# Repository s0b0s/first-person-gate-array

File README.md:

# First-Person Gate Array

A first-person shooter game built entirely from digital logic on a small FPGA board, with no
processor anywhere (no soft CPU, no microcontroller). The 3D renderer, monsters, game rules,
keyboard and mouse interface and sound are all state machines and memories written in VHDL.

## What the game is

Walk through a textured 3D maze, open doors, collect keys, health, ammo and weapons, and fight
monsters that see you, chase you and shoot back. Three levels, the last ending with a boss.
Each level has floor and ceiling heights, steps, ramps and pits, flickering and glowing
lights, outdoor areas with a sky, and animated slime walls. Gunfire wakes monsters in nearby
rooms, except those lying in ambush.

There is a status bar, a minimap, a full-screen automap, title, briefing and score screens,
and stereo sound effects and music.

## How it runs

- **Board:** Digilent Cmod A7-35T (a Xilinx Artix-7 FPGA with 512 KB of external SRAM and 4 MB
  of flash).
- **Video:** 320x240 pixels, each drawn as a 2x2 block on a standard 640x480, 60 Hz VGA monitor
  through a Digilent Pmod VGA. Colors come from a 256-entry palette.
- **Input:** a PS/2 keyboard and a PS/2 mouse through two Digilent Pmod PS2 boards.
- **Sound:** stereo through a Digilent Pmod I2S2 to headphones.
- **Boot:** the design and all game data load from the board's flash at power-up, so no PC is
  needed.

The modules plug into a small custom carrier PCB. Inside the FPGA, the main blocks are:

| Block | What it does |
| --- | --- |
| Ray engine | Casts one ray per screen column through the tile map to find the walls |
| Column rasterizer | Draws each column: walls, floors, ceilings, sky, lighting |
| Sprite engine | Draws monsters, items and projectiles, hidden correctly behind walls |
| Overlay | Status bar, minimap, automap and text screens |
| Game core | Player movement, collision, doors, monsters, weapons, pickups, levels |
| Display controller | Reads the finished frame from SRAM and sends it to the monitor |
| PS/2 host | Talks to the keyboard and mouse |
| Audio mixer | Mixes 8 sound effect voices and a music track |
| SRAM and flash controllers | Shared memory access and loading game data at boot |

Two frames live in SRAM: the game draws one while the monitor shows the other. Drawing takes
about 3 to 6 ms of the 16.8 ms frame (the 25 MHz pixel clock gives 59.5 Hz).

## Controls

| Action | Keys |
| --- | --- |
| Move forward / back | W / S, or the up / down arrows |
| Strafe | A / D |
| Turn | Mouse, or the left / right arrows |
| Fire | Left click, or Ctrl |
| Use (doors, switches) | Space |
| Run | Shift |
| Duck | Hold C |
| Peek left / right | Hold Q / E |
| Weapons | 1, 2, or right click to cycle |
| Automap | Tab |
| Pause | Esc |

## How it was built

The design grew in steps, each ending in a bitstream that builds and meets timing:

| In order | What it added | Top level |
| --- | --- | --- |
| Bring-up | Test patterns, SRAM and flash tests, raw keyboard and mouse codes, test tone, UART | `bringup_top` |
| First maze | A textured maze to walk through, with doors and collision | `game_top` |
| Full game | Monsters, weapons, items, keys, HUD, maps, sound, three levels | `shooter_top` |
| Heights | Floor and ceiling heights, steps, ramps, light effects, sky, animated walls | `shooter_top` |
| Alerts | Monsters woken by gunfire, and ambushing monsters | `shooter_top` |

## How it was checked

A Python model of the whole game (`tools/model/`) is the reference. It generates the
textures, levels and sounds and the "golden" frames, game states and audio samples. Every
hardware block has a self-checking testbench that matches the model bit for bit. The largest
test boots the complete design from a simulated flash chip and plays a scripted session.

## Repository layout

| Folder | Contents |
| --- | --- |
| `rtl/` | The hardware design (VHDL), one block per file |
| `sim/` | Simulation testbenches and models of the SRAM, flash, keyboard, mouse and monitor |
| `constraints/` | Pin assignments and timing constraints for the board |
| `scripts/` | Build the bitstream and run the simulations |
| `tools/` | Python: the game model, asset generators, flash image builder, style checkers, PC debug tools |
| `assets/levels/` | Text pictures of the three level maps, written by the model, so a person can read the levels |
| `build/` | Everything generated (not kept in git) |

## Building

You need Vivado 2025.1 (xsim runs the testbenches) and Python 3.9 or newer. The Python tools
use only the standard library, except the UART tools in `tools/uart/`: the debug tool needs
`pyserial` (`pip install -r requirements.txt`) and the live viewer also `pygame-ce`. With
[uv](https://docs.astral.sh/uv/), `uv run tools/uart/debug_uart.py ...` installs what each needs.
Run everything from the repository root.

On a fresh clone, run the first two steps first: they write the art, level and game-data
files into `build/` that the testbenches and the flash image read.

| Step | Command |
| --- | --- |
| Generate the assets, ROM contents and test data | `python tools/model/build_assets.py` |
| Build the flash game-data image | `python tools/flash_image/make_gamedata.py` |
| Run every testbench (the full-system test sets the pace) | `python scripts/run_sim.py` |
| Run only the testbenches whose inputs changed since they last passed | `python scripts/run_sim.py --changed` |
| Run some testbenches | `python scripts/run_sim.py tb_sram tb_ray_engine` |
| Check the code style | `python tools/style/check_vhdl_style.py` and `python tools/style/check_vhdl_structure.py` |
| Build the bitstream and flash image | `vivado -mode batch -source scripts/build.tcl -tclargs shooter_top` |

The build writes `build/shooter_top/shooter_top.bit` (load straight into the FPGA) and
`shooter_top.mcs` (program into flash so the game boots on its own). `bringup_top` (board and
wiring test pages) and `game_top` (the first playable maze) build the same way.

## Watching the game without a monitor

`tools/uart/live_view.py` (or double-click `tools/uart/live_view.bat`) shows the game in a
window over the board's USB cable, like a second monitor. It finds the board and the link rate
by itself and reconnects when the board is reset, reprogrammed or unplugged; close the window
to stop it. The board streams each new frame at 12 Mbaud, sending only the pixels that changed
since the frame before, run-length encoded, so the window keeps up with the game's 60 frames a
second; a whole new view while turning fast takes longer. Older bitstreams without the stream
command are read frame by frame instead. The keyboard and mouse stay on the board.
`tools/uart/debug_uart.py` reads and writes registers and memory, and its `capture` command
freezes the game for an exact frame dump.

## Art and sound

All textures, sprites, sounds and music are original, generated by `tools/model/`. No assets
from other games are used.

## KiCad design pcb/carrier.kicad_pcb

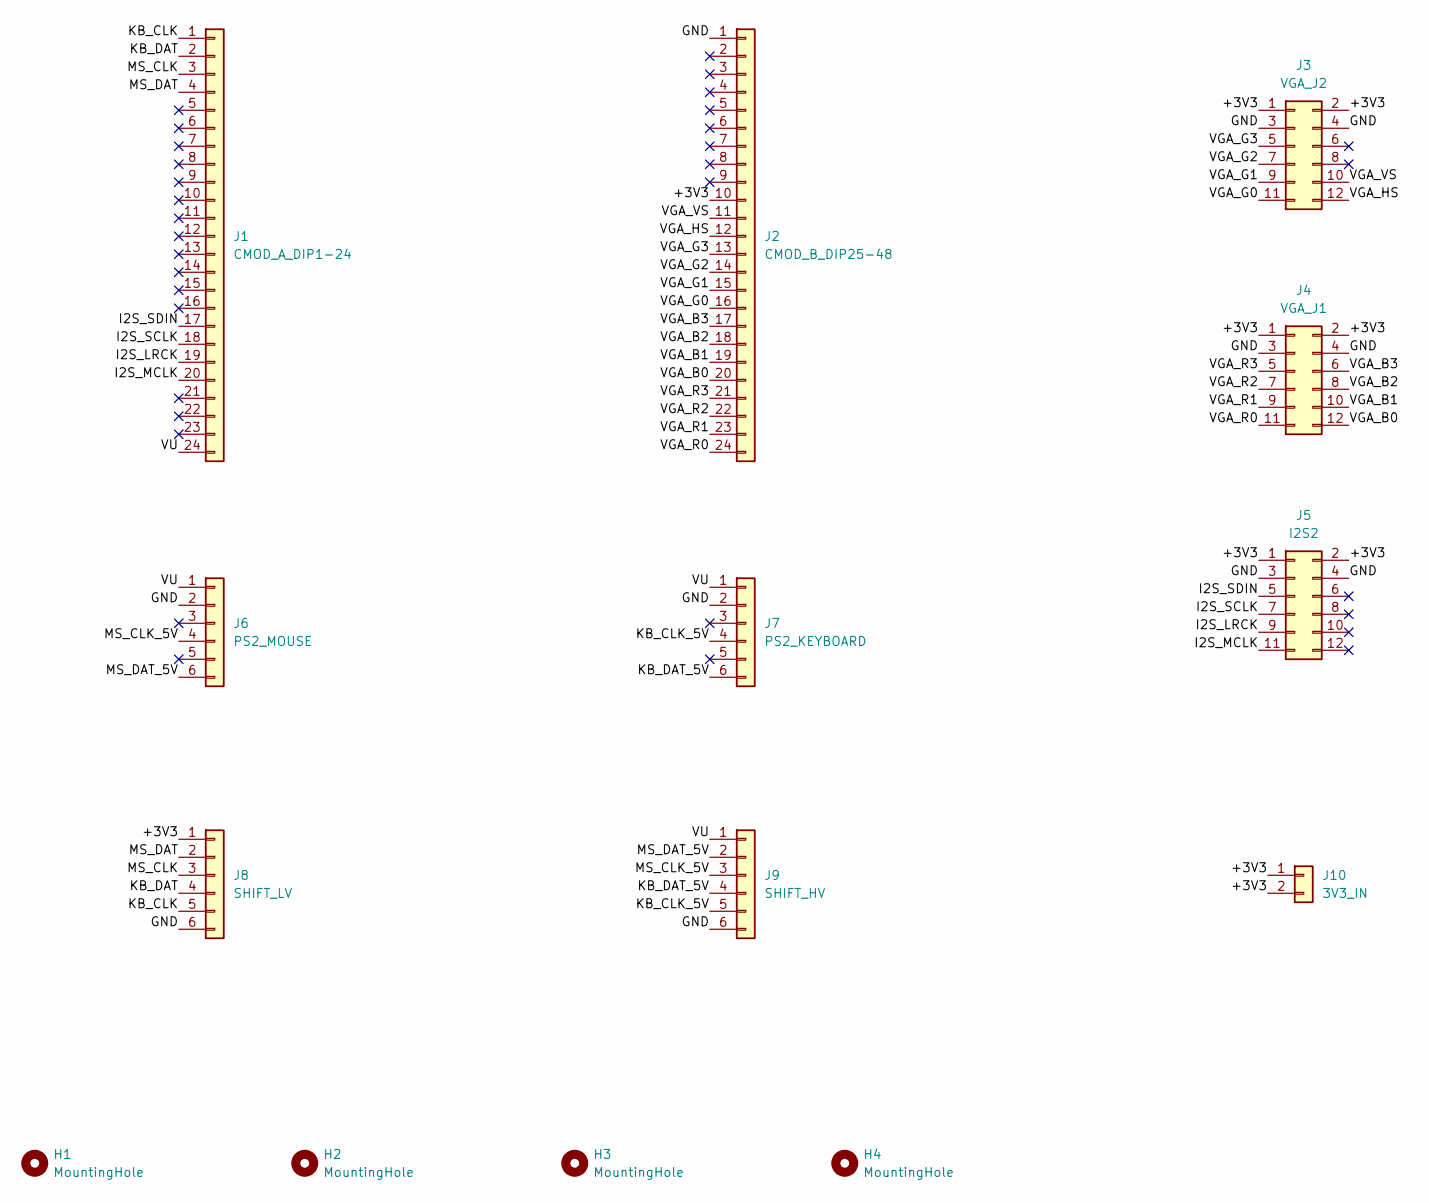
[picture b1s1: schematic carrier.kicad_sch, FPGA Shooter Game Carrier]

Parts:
H1, H2, H3, H4: MountingHole; MountingHole_3.2mm_M3
J1: CMOD_A_DIP1-24; PinSocket_1x24_P2.54mm_Vertical
J2: CMOD_B_DIP25-48; PinSocket_1x24_P2.54mm_Vertical
J3: VGA_J2; PinSocket_2x06_P2.54mm_Horizontal_Edge2mm
J4: VGA_J1; PinSocket_2x06_P2.54mm_Horizontal_Edge2mm
J5: I2S2; PinSocket_2x06_P2.54mm_Horizontal_Edge2mm
J6: PS2_MOUSE; PinSocket_1x06_P2.54mm_Horizontal_Edge2mm
J7: PS2_KEYBOARD; PinSocket_1x06_P2.54mm_Horizontal_Edge2mm
J8: SHIFT_LV; PinSocket_1x06_P2.54mm_Vertical
J9: SHIFT_HV; PinSocket_1x06_P2.54mm_Vertical
J10: 3V3_IN; PinSocket_1x02_P2.54mm_Vertical

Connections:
/+3V3: J2.10, J3.1, J3.2, J4.1, J4.2, J5.1, J5.2, J8.1, J10.1, J10.2
/GND: J2.1, J3.3, J3.4, J4.3, J4.4, J5.3, J5.4, J6.2, J7.2, J8.6, J9.6
/I2S_LRCK: J1.19, J5.9
/I2S_MCLK: J1.20, J5.11
/I2S_SCLK: J1.18, J5.7
/I2S_SDIN: J1.17, J5.5
/KB_CLK: J1.1, J8.5
/KB_CLK_5V: J7.4, J9.5
/KB_DAT: J1.2, J8.4
/KB_DAT_5V: J7.6, J9.4
/MS_CLK: J1.3, J8.3
/MS_CLK_5V: J6.4, J9.3
/MS_DAT: J1.4, J8.2
/MS_DAT_5V: J6.6, J9.2
/VGA_B0: J2.20, J4.12
/VGA_B1: J2.19, J4.10
/VGA_B2: J2.18, J4.8
/VGA_B3: J2.17, J4.6
/VGA_G0: J2.16, J3.11
/VGA_G1: J2.15, J3.9
/VGA_G2: J2.14, J3.7
/VGA_G3: J2.13, J3.5
/VGA_HS: J2.12, J3.12
/VGA_R0: J2.24, J4.11
/VGA_R1: J2.23, J4.9
/VGA_R2: J2.22, J4.7
/VGA_R3: J2.21, J4.5
/VGA_VS: J2.11, J3.10
/VU: J1.24, J6.1, J7.1, J9.1

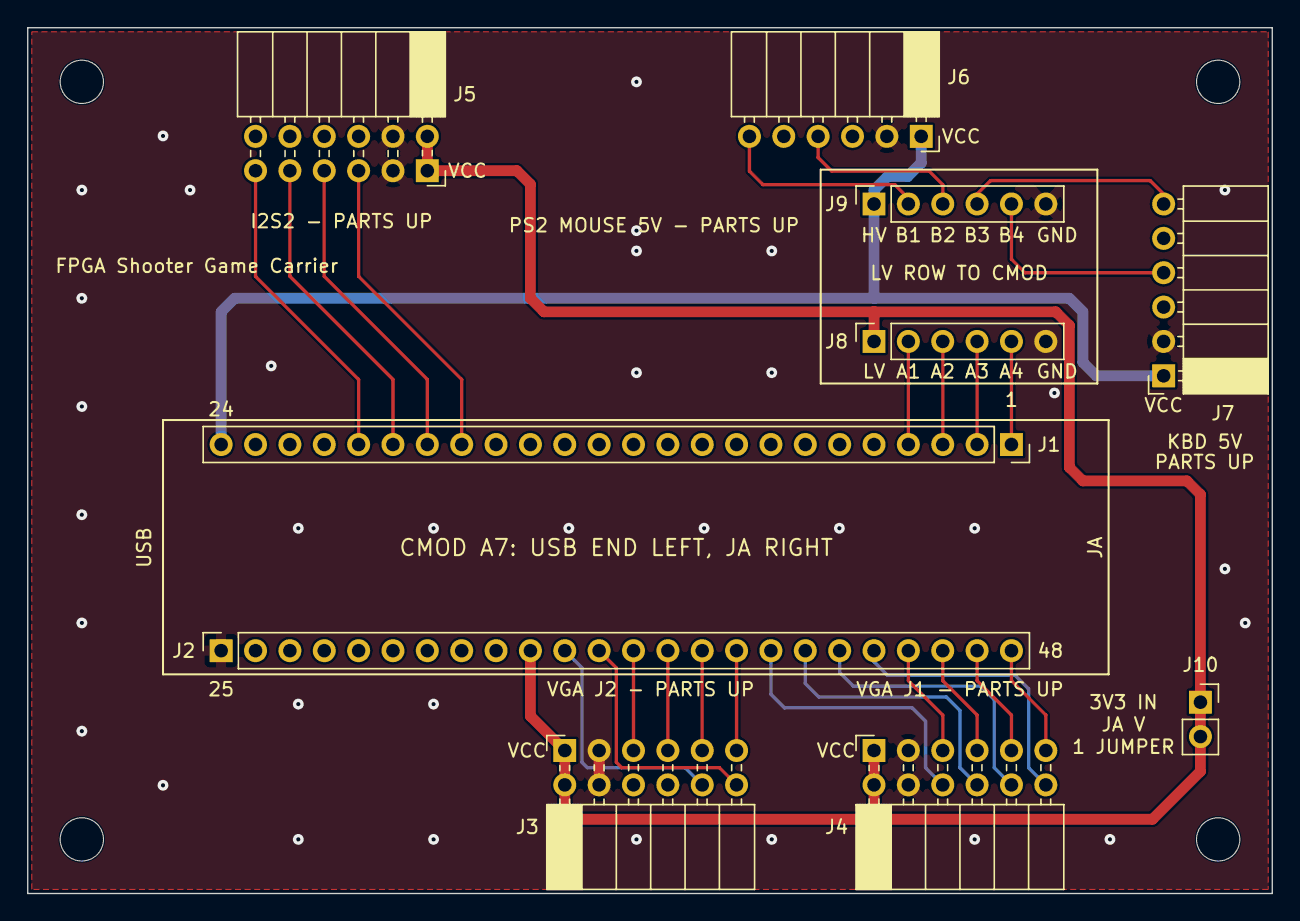
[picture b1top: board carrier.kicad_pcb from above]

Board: 2 copper layers, 92.0 x 64.0 mm, 14 parts (0 on the bottom side), 29 nets.

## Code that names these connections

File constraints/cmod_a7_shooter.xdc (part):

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## resistors are the pull-ups. Channel An (3.3 V) maps to Bn (5 V) on the Pmod
## PS2 socket (Pmod pin 1 Data, 3 Clock).
## DIP 1 kb_clk: A4/B4, keyboard Clock
set_property -dict { PACKAGE_PIN M3 IOSTANDARD LVCMOS33 DRIVE 8 } [get_ports kb_clk]
## DIP 2 kb_dat: A3/B3, keyboard Data
set_property -dict { PACKAGE_PIN L3 IOSTANDARD LVCMOS33 DRIVE 8 } [get_ports kb_dat]
## DIP 3 ms_clk: A2/B2, mouse Clock
set_property -dict { PACKAGE_PIN A16 IOSTANDARD LVCMOS33 DRIVE 8 } [get_ports ms_clk]
## DIP 4 ms_dat: A1/B1, mouse Data
set_property -dict { PACKAGE_PIN K3 IOSTANDARD LVCMOS33 DRIVE 8 } [get_ports ms_dat]

## Pmod I2S2, DAC row only (Pmod pins 1 MCLK, 2 LRCK, 3 SCLK, 4 SDIN). DIP
## order SDIN to MCLK keeps the four PCB traces from crossing.
## DIP 17 -> I2S2 pin 4
set_property -dict { PACKAGE_PIN M1 IOSTANDARD LVCMOS33 SLEW SLOW DRIVE 8 IOB TRUE } [get_ports i2s_sdin]
## DIP 18 -> I2S2 pin 3
set_property -dict { PACKAGE_PIN N3 IOSTANDARD LVCMOS33 SLEW SLOW DRIVE 8 IOB TRUE } [get_ports i2s_sclk]
## DIP 19 -> I2S2 pin 2
set_property -dict { PACKAGE_PIN P3 IOSTANDARD LVCMOS33 SLEW SLOW DRIVE 8 IOB TRUE } [get_ports i2s_lrck]
## DIP 20 -> I2S2 pin 1
set_property -dict { PACKAGE_PIN M2 IOSTANDARD LVCMOS33 SLEW SLOW DRIVE 8 IOB TRUE } [get_ports i2s_mclk]

## PWR_SENSE: the PCB 3.3 V net; pulled down so a missing jumper reads '0'
set_property -dict { PACKAGE_PIN W3 IOSTANDARD LVCMOS33 PULLDOWN TRUE } [get_ports pwr_sense]

## Pmod VGA: slow edges for unterminated traces, IOB registers so all bits
## change together
set_property -dict { PACKAGE_PIN V3 IOSTANDARD LVCMOS33 } [get_ports vga_vs]
set_property -dict { PACKAGE_PIN W5 IOSTANDARD LVCMOS33 } [get_ports vga_hs]
set_property -dict { PACKAGE_PIN V4 IOSTANDARD LVCMOS33 } [get_ports {vga_g[3]}]
set_property -dict { PACKAGE_PIN U4 IOSTANDARD LVCMOS33 } [get_ports {vga_g[2]}]
set_property -dict { PACKAGE_PIN V5 IOSTANDARD LVCMOS33 } [get_ports {vga_g[1]}]
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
